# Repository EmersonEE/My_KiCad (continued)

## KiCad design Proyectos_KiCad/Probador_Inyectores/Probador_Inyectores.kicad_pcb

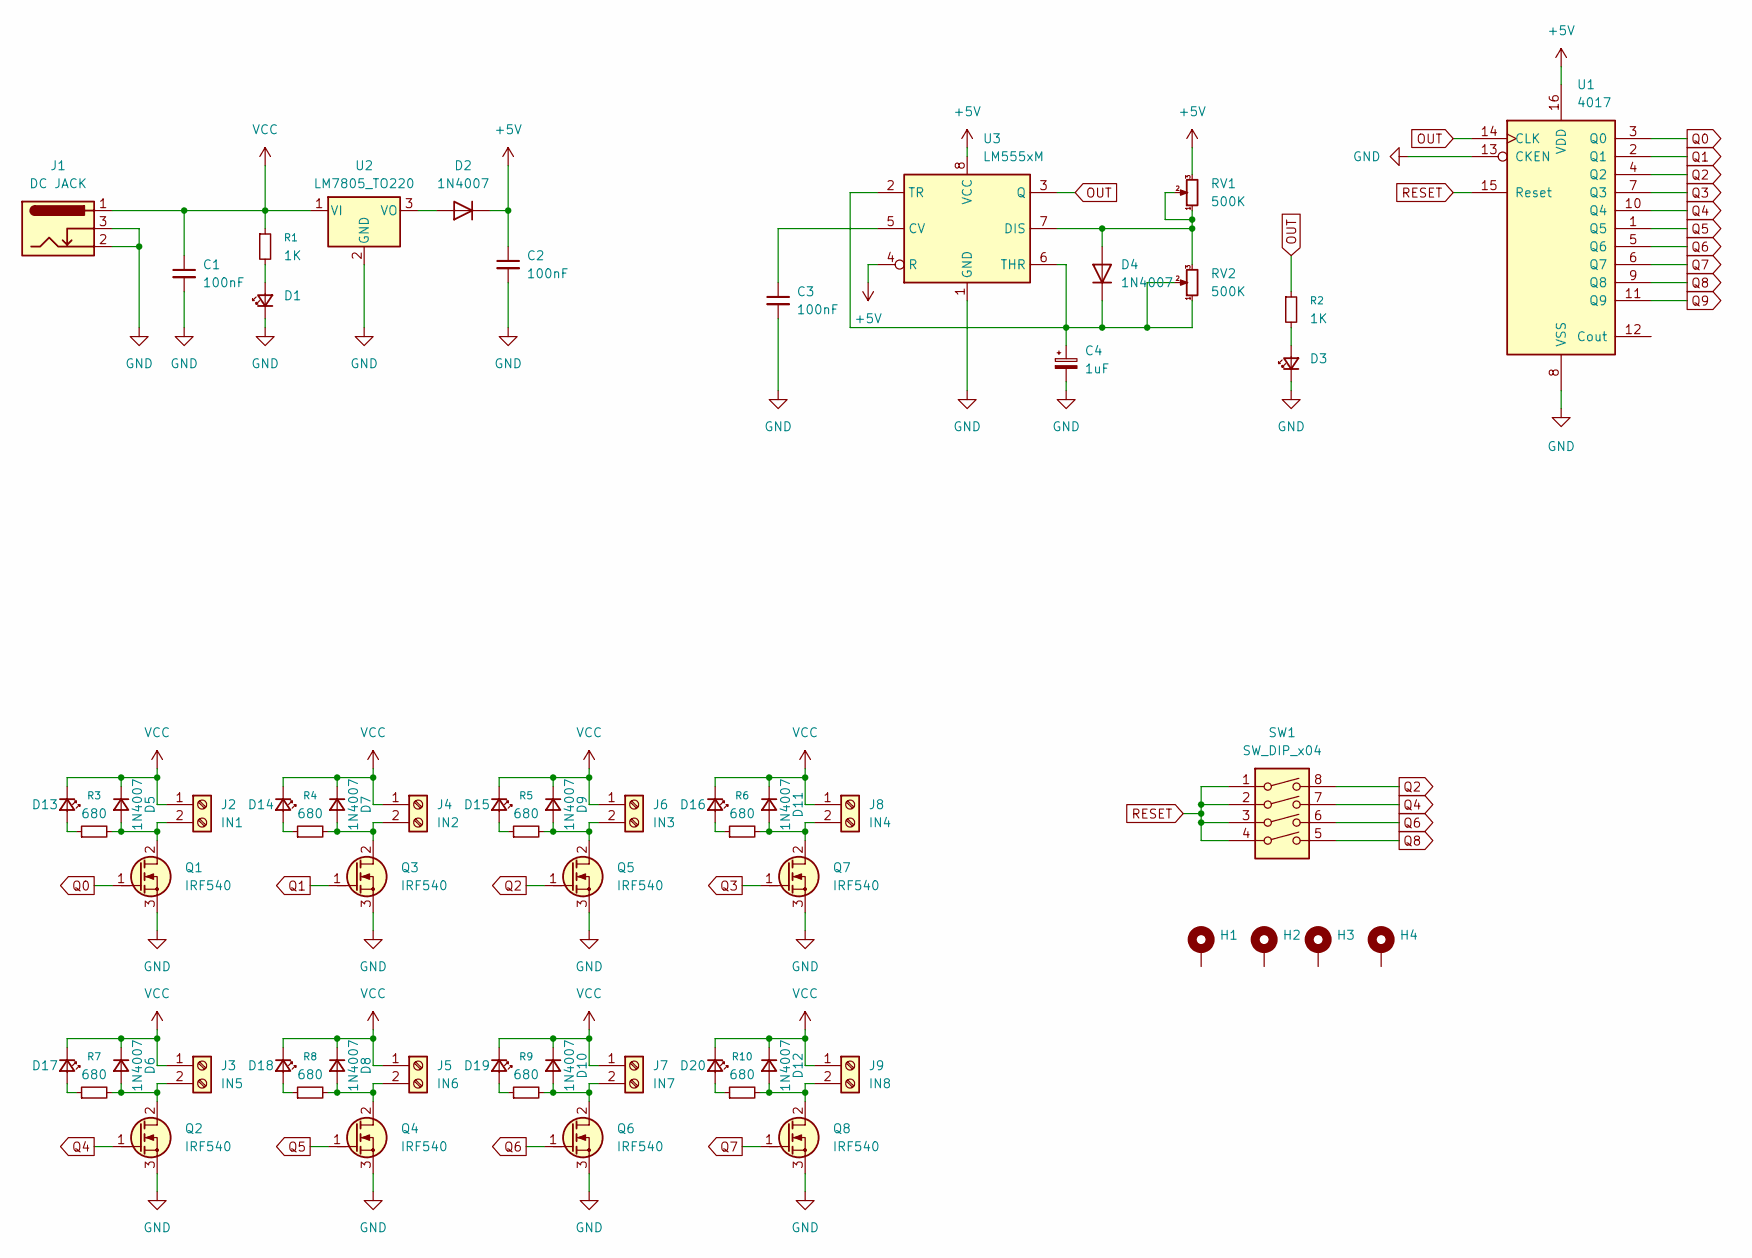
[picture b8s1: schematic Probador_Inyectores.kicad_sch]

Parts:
C1, C2, C3: 100nF; C_Disc_D3.8mm_W2.6mm_P2.50mm
C4: 1uF; CP_Radial_D5.0mm_P2.50mm
D1, D3: LED_D5.0mm
D2, D4: 1N4007; D_DO-41_SOD81_P10.16mm_Horizontal
D5, D6, D7, D8, D9, D10, D11, D12: 1N4007; D_SMA
D13, D14, D15, D16, D17, D18, D19, D20: LED_D3.0mm
H1, H2, H3, H4: MountingHole_3.2mm_M3_Pad_Via
J1: DC JACK; BarrelJack_Horizontal
J2: IN1; TerminalBlock_Phoenix_MKDS-1,5-2-5.08_1x02_P5.08mm_Horizont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
J3: IN5; TerminalBlock_Phoenix_MKDS-1,5-2-5.08_1x02_P5.08mm_Horizont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
J4: IN2; TerminalBlock_Phoenix_MKDS-1,5-2-5.08_1x02_P5.08mm_Horizont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
J5: IN6; TerminalBlock_Phoenix_MKDS-1,5-2-5.08_1x02_P5.08mm_Horizont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
J6: IN3; TerminalBlock_Phoenix_MKDS-1,5-2-5.08_1x02_P5.08mm_Horizont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
J7: IN7; TerminalBlock_Phoenix_MKDS-1,5-2-5.08_1x02_P5.08mm_Horizont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
J8: IN4; TerminalBlock_Phoenix_MKDS-1,5-2-5.08_1x02_P5.08mm_Horizont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
J9: IN8; TerminalBlock_Phoenix_MKDS-1,5-2-5.08_1x02_P5.08mm_Horizont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
Q1, Q2, Q3, Q4, Q5, Q6, Q7, Q8: IRF540; TO-220-3_Vertical_GDS
R1, R2: 1K
R3, R4, R5, R6, R7, R8, R9, R10: 680; R_0805_2012Metric_Pad1.15x1.40mm
RV1, RV2: 500K; Potentiometer_Alps_RK163_Single_Horizontal
SW1: SW_DIP_x04; SW_DIP_SPSTx04_Slide_9.78x12.34mm_W7.62mm_P2.54mm
U1: 4017; DIP-16_W7.62mm_LongPads
U2: LM7805_TO220; TO-220-3_Vertical
U3: LM555xM; DIP-8_W7.62mm_LongPads

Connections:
+5V: C2.1, D2.1 (K), RV1.3, U1.16 (VDD), U3.4 (R), U3.8 (VCC)
GND: C1.2, C2.2, C3.2, C4.2, D1.1 (K), D3.1 (K), J1.2, J1.3, Q1.3 (S), Q2.3 (S), Q3.3 (S), Q4.3 (S), Q5.3 (S), Q6.3 (S), Q7.3 (S), Q8.3 (S), U1.8 (VSS), U1.13 (CKEN), U2.2 (GND), U3.1 (GND)
unnamed: D1.2 (A), R1.2
unnamed: D2.2 (A), U2.3 (VO)
unnamed: D3.2 (A), R2.2
unnamed: D4.2 (A), RV1.1, RV1.2, RV2.3, U3.7 (DIS)
unnamed: C4.1, D4.1 (K), RV2.1, RV2.2, U3.2 (TR), U3.6 (THR)
unnamed: D5.2 (A), J2.2, Q1.2 (D), R3.2
unnamed: D6.2 (A), J3.2, Q2.2 (D), R7.2
unnamed: D7.2 (A), J4.2, Q3.2 (D), R4.2
unnamed: D8.2 (A), J5.2, Q4.2 (D), R8.2
unnamed: D9.2 (A), J6.2, Q5.2 (D), R5.2
unnamed: D10.2 (A), J7.2, Q6.2 (D), R9.2
unnamed: D11.2 (A), J8.2, Q7.2 (D), R6.2
unnamed: D12.2 (A), J9.2, Q8.2 (D), R10.2
unnamed: D13.2 (A), R3.1
unnamed: D14.2 (A), R4.1
unnamed: D15.2 (A), R5.1
unnamed: D16.2 (A), R6.1
unnamed: D17.2 (A), R7.1
unnamed: D18.2 (A), R8.1
unnamed: D19.2 (A), R9.1
unnamed: D20.2 (A), R10.1
unnamed: C3.1, U3.5 (CV)
OUT: R2.1, U1.14 (CLK), U3.3 (Q)
Q0: Q1.1 (G), U1.3 (Q0)
Q1: Q3.1 (G), U1.2 (Q1)
Q2: Q5.1 (G), SW1.8, U1.4 (Q2)
Q3: Q7.1 (G), U1.7 (Q3)
Q4: Q2.1 (G), SW1.7, U1.10 (Q4)
Q5: Q4.1 (G), U1.1 (Q5)
Q6: Q6.1 (G), SW1.6, U1.5 (Q6)
Q7: Q8.1 (G), U1.6 (Q7)
Q8: SW1.5, U1.9 (Q8)
Q9: U1.11 (Q9)
RESET: SW1.1, SW1.2, SW1.3, SW1.4, U1.15 (Reset)
VCC: C1.1, D5.1 (K), D6.1 (K), D7.1 (K), D8.1 (K), D9.1 (K), D10.1 (K), D11.1 (K), D12.1 (K), D13.1 (K), D14.1 (K), D15.1 (K), D16.1 (K), D17.1 (K), D18.1 (K), D19.1 (K), D20.1 (K), J1.1, J2.1, J3.1, J4.1, J5.1, J6.1, J7.1, J8.1, J9.1, R1.1, U2.1 (VI)

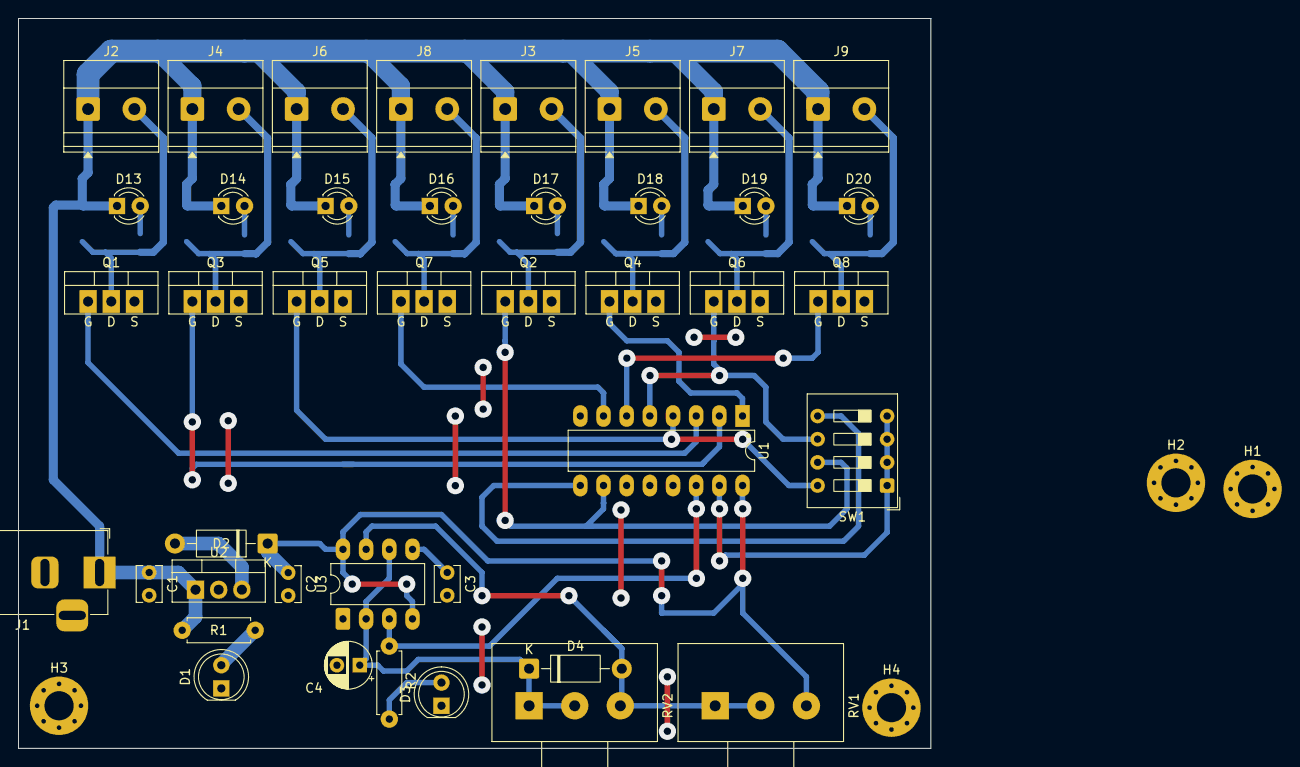
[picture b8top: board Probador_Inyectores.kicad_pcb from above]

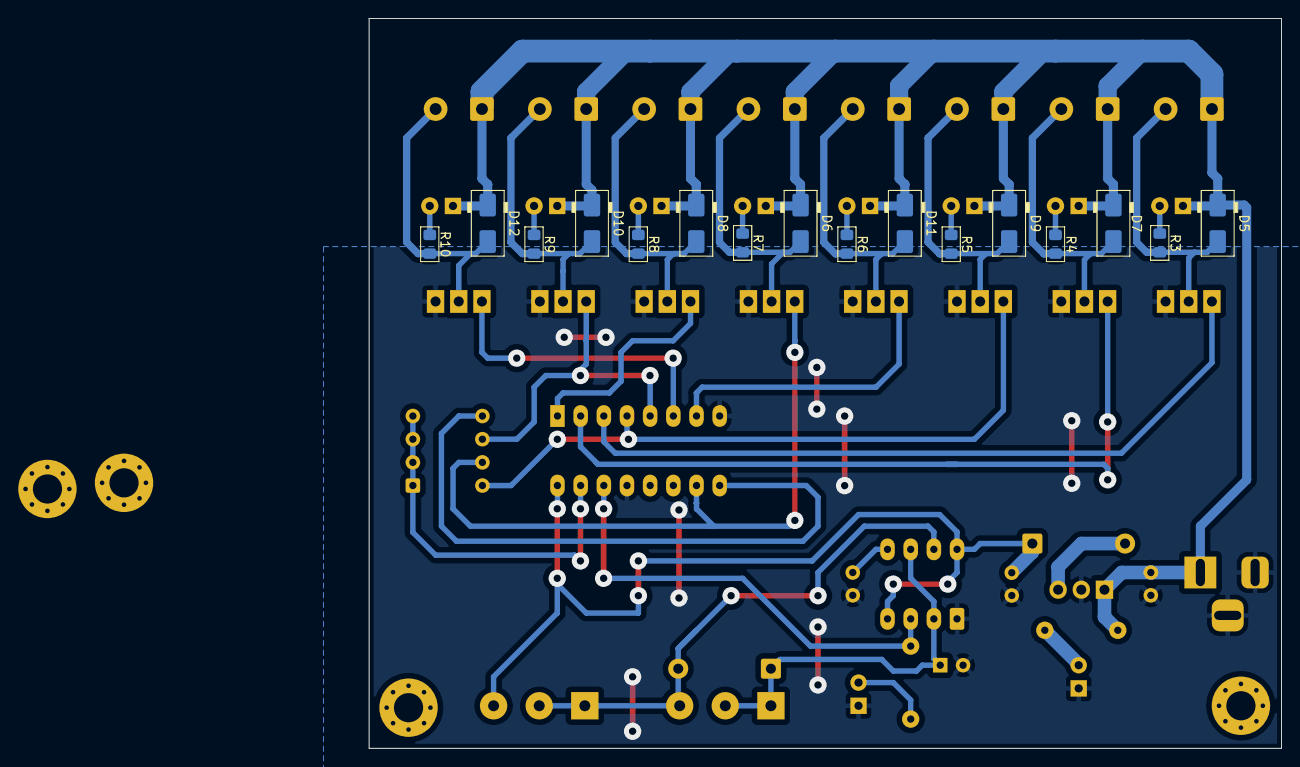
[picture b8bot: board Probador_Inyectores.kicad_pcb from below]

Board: 2 copper layers, 100.0 x 80.0 mm, 61 parts (16 on the bottom side), 36 nets.
